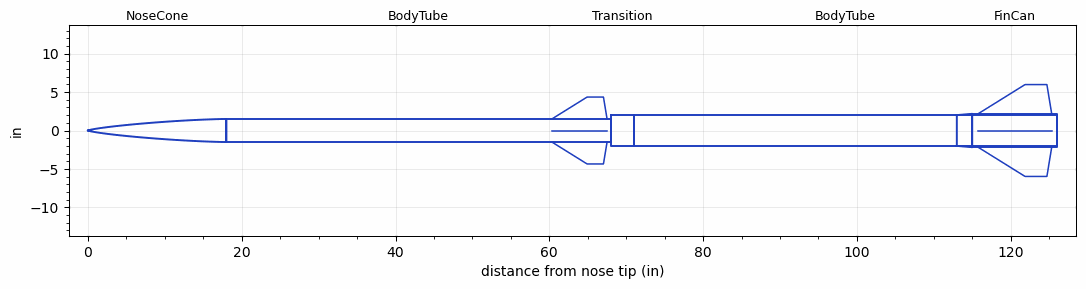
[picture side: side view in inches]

<RASAeroDocument>
 <FileVersion>2</FileVersion>
 <RocketDesign>
  <NoseCone>
   <Length>18</Length>
   <Diameter>3</Diameter>
   <Shape>Von Karman Ogive</Shape>
   <Location>0</Location>
  </NoseCone>
  <BodyTube>
   <Length>50</Length>
   <Diameter>3</Diameter>
   <Location>18</Location>
   <Fin>
    <Count>4</Count>
    <Chord>7.1775</Chord>
    <Span>2.85</Span>
    <SweepDistance>4.58</SweepDistance>
    <TipChord>2.13</TipChord>
    <Thickness>0.25</Thickness>
    <LERadius>0.08</LERadius>
    <Location>7.67</Location>
    <AirfoilSection>Hexagonal</AirfoilSection>
    <FX1>0.5</FX1>
    <FX3>0.5</FX3>
   </Fin>
  </BodyTube>
  <Transition>
   <Length>3</Length>
   <Diameter>4</Diameter>
   <Location>68</Location>
   <RearDiameter>4</RearDiameter>
  </Transition>
  <BodyTube>
   <Length>55</Length>
   <Diameter>4</Diameter>
   <Location>71</Location>
  </BodyTube>
  <FinCan>
   <Length>11</Length>
   <Diameter>4.35</Diameter>
   <InsideDiameter>4</InsideDiameter>
   <Location>126</Location>
   <ShoulderLength>2</ShoulderLength>
   <Offset>-11</Offset>
   <Fin>
    <Count>4</Count>
    <Chord>9.57</Chord>
    <Span>3.8</Span>
    <SweepDistance>6.105</SweepDistance>
    <TipChord>2.84</TipChord>
    <Thickness>0.25</Thickness>
    <LERadius>0.08</LERadius>
    <Location>10.23</Location>
    <AirfoilSection>Hexagonal</AirfoilSection>
    <FX1>0.5</FX1>
    <FX3>0.5</FX3>
   </Fin>
  </FinCan>
  <Surface>Smooth (Zero Roughness)</Surface>
  <ModifiedBarrowman>False</ModifiedBarrowman>
  <Turbulence>False</Turbulence>
  <UseBooster1>False</UseBooster1>
  <UseBooster2>False</UseBooster2>
 </RocketDesign>
 <LaunchSite>
  <Altitude>3000</Altitude>
  <Pressure>0</Pressure>
  <RodAngle>0</RodAngle>
  <RodLength>18</RodLength>
  <Temperature>85</Temperature>
  <WindSpeed>8</WindSpeed>
 </LaunchSite>
 <Recovery>
  <Altitude1>1000</Altitude1>
  <Altitude2>1000</Altitude2>
  <DeviceType1>None</DeviceType1>
  <DeviceType2>None</DeviceType2>
  <Event1>False</Event1>
  <Event2>False</Event2>
  <Size1>1</Size1>
  <Size2>1</Size2>
  <EventType1>None</EventType1>
  <EventType2>None</EventType2>
  <CD1>1.33</CD1>
  <CD2>1.33</CD2>
 </Recovery>
</RASAeroDocument>
